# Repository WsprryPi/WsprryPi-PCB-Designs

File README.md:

# WsprryPi PCB Designs

KiCad schematics, PCB layouts, local libraries, and engineering documentation for WsprryPi and Raspberry Pi Pico projects.

See each project's order status, assembly requirements, and validation limits before fabrication. KiCad source files are authoritative; included PDFs are reference exports and may not match the current sources.

## Experimental use and warranty

All designs are provided **as is, without warranty**, as stipulated by the [MIT license](LICENSE.md) for repository-owned work. These are experimental hardware systems. They should not be used for production work unless the operator understands the design's limitations, assembly and power requirements, calibration needs, and the validation required for the actual system and operating conditions.

The operator is responsible for determining suitability and verifying the assembled hardware. A clean CAD check or a fabrication-ready layout does not establish electrical, RF, thermal, mechanical, or system performance. Third-party assets retain their documented licenses and notices.

## Projects

| Project | Purpose | Status / reference export |
| --- | --- | --- |
| [WsprryPi LPF](WsprryPi%20LPF/README.md) | Low-pass filter board and design workbook | Export from the KiCad source |
| [Pico 2W Wattmeter Shield](Pico%202W%20Wattmeter%20Shield/README.md) | ADL5904 RF detector and ADS1115 ADC shield | See project assembly drawings |
| [Pico 2W Shield Template](Pico%202W%20Shield%20Template/README.md) | Unwired shield interface, outline, and antenna notch | KiCad project template |
| [WsprryPico GPIO Shield](WsprryPico%20GPIO%20Shield/README.md) | Pico 2 W shield with the grouped BS170 amplifier circuit and independent local libraries | Placed and routed GPIO design; see current validation |
| [WsprryPico Synth Shield with GPS](WsprryPico%20Synth%20Shield%20with%20GPS/README.md) | Pico 2 W TCXO/Si5351A shield with a BS170 amplifier and onboard GNSS | Implemented PCB for the 2200 m–10 m target; see current validation and bias setup |
| [QRP Labs Modules](QRP%20Labs%20Modules/README.md) | Electrical models of the photographed 25 MHz TCXO and Rev6 synthesizer, with their interconnection | [Reference schematic PDF](QRP%20Labs%20Modules/QRP%20Labs%20Modules.pdf); separate from the proposed synth shield |
| [RPi Full-Size HAT Template](RPi%20Full-Size%20HAT%20Template/README.md) | Official full-size HAT geometry and complete 40-pin interface | KiCad project template |
| [RPi Zero HAT Template](RPi%20Zero%20HAT%20Template/README.md) | Zero-size uHAT geometry and complete HAT+ capable 40-pin interface | KiCad project template |
| [WsprryPi Zero GPIO BS170](WsprryPi%20Zero%20GPIO%20BS170/README.md) | Zero-size Raspberry Pi GPIO RF amplifier with a single BS170 | **Ready for order:** headers and BS170 fitted by hand after manufacture; see [fabrication and assembly notes](WsprryPi%20Zero%20GPIO%20BS170/FABRICATION-NOTES.md) |

[Project-local Pico 2 W library assets](Pico%202W%20Wattmeter%20Shield/pico-2w-libs/README.md) include a symbol, footprints, and STEP model with documented compatibility and provenance limits. They are stored inside the Wattmeter Shield project; the Shield Template uses its own independent local libraries.

## Open a design

Clone [WsprryPi/WsprryPi-PCB-Designs](https://github.com/WsprryPi/WsprryPi-PCB-Designs) into a folder named `WsprryPi PCB Designs` and open the project's `.kicad_pro` file in KiCad. Read its README for assembly requirements, dependencies, and validation limits. Follow the applicable template's instructions to create a new shield or HAT project.

| Project | Saved schematic and PCB generator version |
| --- | --- |
| WsprryPi LPF, Pico 2W Wattmeter Shield, Pico 2W Shield Template, WsprryPico GPIO Shield, WsprryPico Synth Shield with GPS, RPi Full-Size HAT Template, RPi Zero HAT Template, WsprryPi Zero GPIO BS170 | KiCad 10.0 |

Project library tables use `${KIPRJMOD}` paths. Keep each project's local libraries together when copying it. The Pico and HAT projects use their own local libraries and installed KiCad models where their project documentation specifies them.

### Project-local libraries

The LPF includes local copies of its symbols and footprints, plus available STEP models, resolved through `${KIPRJMOD}`. Its local library assets require KiCad 10.0.1 or newer; the generator version above describes its saved format. The other projects maintain their own independent local libraries as described in their READMEs.

- [LPF library contents and limits](WsprryPi%20LPF/libraries/README.md)
- [BS170 amplifier library sources and limits](WsprryPi%20Zero%20GPIO%20BS170/LIBRARY-SOURCES.md)

Project documentation records model gaps, assembly exclusions, and the applicability of ERC/DRC findings to the identified source revision. Order readiness does not establish measured electrical, thermal, or RF performance.

## Design proposals

These documents describe proposed circuits and outstanding engineering requirements; they do not establish implemented or validated hardware.

- [GPS frequency calibration for Pi and Pico](design/GPS-FREQUENCY-CALIBRATION.md): LS7366R capture of Si5351 CLK2 against GPS PPS.
- [Broadband RF amplifier HAT](design/raspberry-pi-hat-broadband-rf-amplifier.md): a proposed clock-input amplifier, power control, and supply architecture.

## Repository contents

Track design sources, local libraries, reusable models, design calculations, intentional reference exports, and documentation. Preserve legacy cache or rescue libraries required by a design.

The root [`.gitignore`](.gitignore) covers KiCad local preferences, locks, caches, automatic backups, `.history`, and `jlcpcb/` plugin state and output throughout the repository. Put regenerable exports in `generated/`, `production/`, or `fabrication/`.

Publish manufacturing packages with the corresponding GitHub release, identifying the source commit, board revision, KiCad version, and validation status. Keep assembly and fabrication requirements in the project's maintained documentation.

## Contributions and license

See [CONTRIBUTING.md](CONTRIBUTING.md) for editing and validation requirements. Report problems through [GitHub Issues](https://github.com/WsprryPi/WsprryPi-PCB-Designs/issues). [AGENTS.md](AGENTS.md) contains shared agent guidance; [CLAUDE.md](CLAUDE.md) points to it.

Repository-owned work uses the [MIT license](LICENSE.md). Preserve third-party copyright, attribution, and license terms; project and library documentation identifies known exceptions and provenance limits.

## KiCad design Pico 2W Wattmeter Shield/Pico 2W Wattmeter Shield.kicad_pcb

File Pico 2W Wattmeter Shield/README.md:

# Pico 2W QRP Wattmeter Shield

A Raspberry Pi Pico 2 W shield with an ADL5904 RF power detector, ADS1115 ADC, and TPS7A2033 analog regulator. Open [Pico 2W Wattmeter Shield.kicad_pro](Pico%202W%20Wattmeter%20Shield.kicad_pro) in KiCad 10. Project libraries use `${KIPRJMOD}` paths.

The design is supplied **as is, without warranty**, under the repository's [MIT license](../LICENSE.md). It is an experimental system. Production use requires an operator who understands its limitations and requirements and verifies the assembled system's suitability. See the [repository notice](../README.md#experimental-use-and-warranty).

## Current design

The PCB is a two-layer, nominally 1.6 mm FR4 board with circuit components on F.Cu and U10's two female socket strips on B.Cu, matching the [Pico shield template](../Pico%202W%20Shield%20Template/README.md). It contains **37 footprints: 34 automatic SMT components, J30, U10, and one front silkscreen logo**. The components, including the R63/C61 pull-up supply filter, are placed and routed.

Assembled input match, accuracy, noise rejection, mechanical fit, and the soldering process are unqualified. ERC ignores single-use global labels, four-way junctions, simulation model issues, and footprint-filter mismatches; DRC has no ignored checks.

## Measurement path

`J30 → C30–C34 → RF_DET_IN → C40–C44 → RFIN/U40 → VRMS_RAW → R50/C50 → VRMS_FILTERED/U60 AIN0`

| Section | Saved design |
| --- | --- |
| RF input | J30; terminating low-power meter, with external attenuation for amplifier outputs |
| Coupling | Two banks of five parallel 100 nF C0G capacitors, nominally 500 nF per bank |
| Shunt load | R30–R34: five parallel 412 Ω resistors, nominally 82.4 Ω, plus the detector input branch |
| Input matching | The shunt is within 0.12% of ADI's 82.5 Ω reference; assembled input impedance is unmeasured |
| Intended frequency range | 136 kHz–450 MHz, covering 2200 m through 70 cm; assembled-board coverage is unqualified |
| Nominal detector range | −30 to +15 dBm, approximately 1 µW–31.6 mW; connector range requires calibration |
| ADC filter | R50 = 470 Ω, C50 = 22 µF X5R; nominal cutoff 15.4 Hz |

There is no onboard attenuation pad or qualified high-power overload protection. The two capacitor banks, buses, launch, and detector impedance form a frequency-dependent RF network. See [input range and measurement conditions](INPUT-RANGE.md). The printed current range is calculated for a nominal 50 Ω load, rather than a direct current measurement.

## Power

**The analog section requires VBUS.** U20 takes VBUS from Pico pin 40 and generates `ANALOG_3V3` for U40, U60, and the I²C pullups. C20 and C21 are 2.2 µF, 25 V X7R capacitors at the regulator input and output. C46/C47 decouple the detector, and C60 decouples the ADC. The Pico's 3V3 output is not connected to the analog rail.

USB normally supplies VBUS. Powering the Pico solely through VSYS leaves the analog section unpowered. An external VBUS source must respect the Pico's USB power arrangement and avoid conflicting supplies. Measurements require a valid analog rail and settled detector/filter output.

VBUS follows the lower perimeter, and the analog rail reaches the detector from below and the ADC/control branch from the right. Neither supply trace crosses the RF capacitor-bank area. R63/C61 isolate the pull-up supply branch. A common regulator and ground serve the analog and I²C loads; noise immunity to Pico activity is unmeasured.

## ADC and filtering

U60 uses AIN0 as a single-ended detector-voltage input. ADDR is grounded, giving I²C address 0x48. SDA uses GP4; SCL uses GP5 through the fitted R62 0 Ω jumper. R60/R61 are 4.7 kΩ pullups supplied through R63 = 47 Ω, with C61 = 1 µF X7R providing local bypass at their common supply node. This filter is present in both schematic and PCB. U40 and U60 receive `ANALOG_3V3` directly with their own decoupling. Unused ADC channels and ALERT/RDY have no-connect flags.

R63/C61 has a nominal **3.4 kHz** corner and approximately **65 mV** supply drop with both pull-ups low, assuming ideal low output levels. It provides local storage and supply isolation for switching currents. Its effect on the assembled noise floor is unmeasured; nominal attenuation at 50/60 Hz is negligible.

R50/C50 passes DC and attenuates changing voltage. Its ideal one-pole attenuation is about **10.6 dB at 50 Hz and 12.1 dB at 60 Hz**, with a 10.34 ms time constant and about 47.6 ms settling to 1%. Capacitor tolerance, bias, temperature, detector output impedance, and ADC loading affect these figures. It is not a mains notch filter, and there is no established system-level mains-rejection specification. C49 remains a separate 10 nF capacitor directly on VRMS.

The hardware provides one measurement channel. ADC range, conversion rate, timed averaging, and calibration coefficients are application settings; this repository does not establish a verified wattmeter firmware configuration.

## Current assembly and fabrication

Factory assembly comprises **34 components on F.Cu**: **C20–C21, C30–C34, C40–C50, C60–C61; R30–R34, R40, R50, R60–R63; U20, U40, U60**. This is 20 capacitors, 11 resistors, and three ICs. J30, two female sockets, and the Pico module are fitted by hand. U10 represents the combined 40-pad socket interface; schematic J10/J11 are pinless purchasing descriptions. The front logo and manual parts are excluded from automatic SMT assembly.

The **Shield purchasing BOM** preset uses `LCSC Part #`. All 34 schematic and PCB SMT parts have matching manufacturer, MPN, and LCSC identifiers. R30–R34 specify Viking ARG02BTC4120 / C2683017 in local 0402 footprints. R63 specifies YAGEO RC0402FR-0747RL / C137973 in 0402; C61 specifies YAGEO CC0603KRX7R8BB105 / C106858 in 0603. Factory BOM and placement exports must contain the same 34 references and correct U20/U40/U60 pin-1 orientation. The schematic contains the complete part selections. The input-range silkscreen displays J30 through a reference variable and follows reannotation.

Seven selected through vias use **0.60 mm copper / 0.25 mm drill** with filling/capping enabled, F-side untented, and B-side tented: five in U40's exposed ground pad and one each centered on R40 pad 1 and C48 pad 1. The unique drill size identifies this selective process. The 17 ordinary vias comprise five 0.50/0.20 mm, ten 0.60/0.30 mm, and two 0.80/0.40 mm vias. All 24 are through vias; the custom rules disallow blind, buried, and microvias. The ordinary ground-via drills beside C45/C47 have **0.15 mm nominal clearance** from the adjacent component solder-pad openings.

The required fabrication process is selective nonconductive epoxy filling, planarization, and copper capping. Its availability for this exact two-layer order is not confirmed. Four separate 0.65 × 0.65 mm F.Paste windows cover 52.16% of U40's 1.8 × 1.8 mm ground land. Supplier process acceptance, stencil thickness, and reflow conditions are assembly requirements.

- [Fabrication and assembly requirements](manufacturing-notes/ORDER-NOTES.txt)
- [Front assembly map](manufacturing-notes/ASSEMBLY-FRONT.svg)
- [Selective via-treatment drawing](manufacturing-notes/U1-VIA-TREATMENT.svg)
- [U40 exposed-pad and stencil geometry](U1-PASTE-WINDOWS.md)
- [SMA connector and board-edge fit](J1-CONNECTOR-NOTES.md)
- [Pico sockets and antenna notch](PICO-HEADERS-AND-NOTCH.md)

The manufacturing drawings identify their source PCB by SHA-256. Socket lead fit and mating height are unspecified. The PCB stackup's copper-finish field is `None`, and there are no dedicated board fiducials; finish and panel tooling belong in the order specification.

## Pico interface placement

U10 is locked at **(146.810, 90.750) mm, −90°, B.Cu**, and its `Raspberry Pi Pico 2W` group is locked. Its 40 pad positions match the template. The notch spans x = 164.46–173.46 mm and y = 82.86–96.86 mm, with a copper/component keepout on both layers.

In **Update PCB from Schematic**, leave **Re-link footprints to schematic symbols based on their reference designators** and **Override locks** unchecked. Normal symbol-ID matching preserves the interface identity and placement. [KiCad's update documentation](https://docs.kicad.org/10.0/en/pcbnew/pcbnew.html#updating_the_board_from_the_schematic) describes these options.

The two socket models belong to U10's combined footprint and use project-local paths. The reusable footprint contains the same references. The socket geometry is a generic preview, without a selected manufacturer or qualified mating stack.

## Libraries and 3D view

Local assets are in `pico-wattmeter.pretty/`, `pico-wattmeter.kicad_sym`, `pico-wattmeter.kicad_blocks/`, and `pico-wattmeter.3dshapes/`. See [footprint sources and licenses](pico-wattmeter.pretty/LIBRARY-SOURCES.md) and [model sources and limits](pico-wattmeter.3dshapes/README.md).

Select **View > 3D Viewer** in the PCB Editor. U40 uses the local CP-16-22 STEP model. U10 uses two local socket models. J30 uses the local illustrative Adafruit 1865 SMA model, pointing outward from the left board edge. Passives, U20, and U60 use installed KiCad models. All placed model references resolve in the checked KiCad installation.

The optional, unplaced Pico SMD footprint uses `${KIPRJMOD}/pico-2w-libs/Raspberrypi pico2 W.step`. That separate reference collection has [pin/pad, model-alignment, and provenance limitations](pico-2w-libs/README.md). It is not the placed socket interface.

`fabrication-toolkit-options.json` stores export preferences. KiCad sources contain the part identifiers, connectivity, layout, and assembly exclusions. Local preferences, backups, plugin state, and generated export directories are ignored by Git.

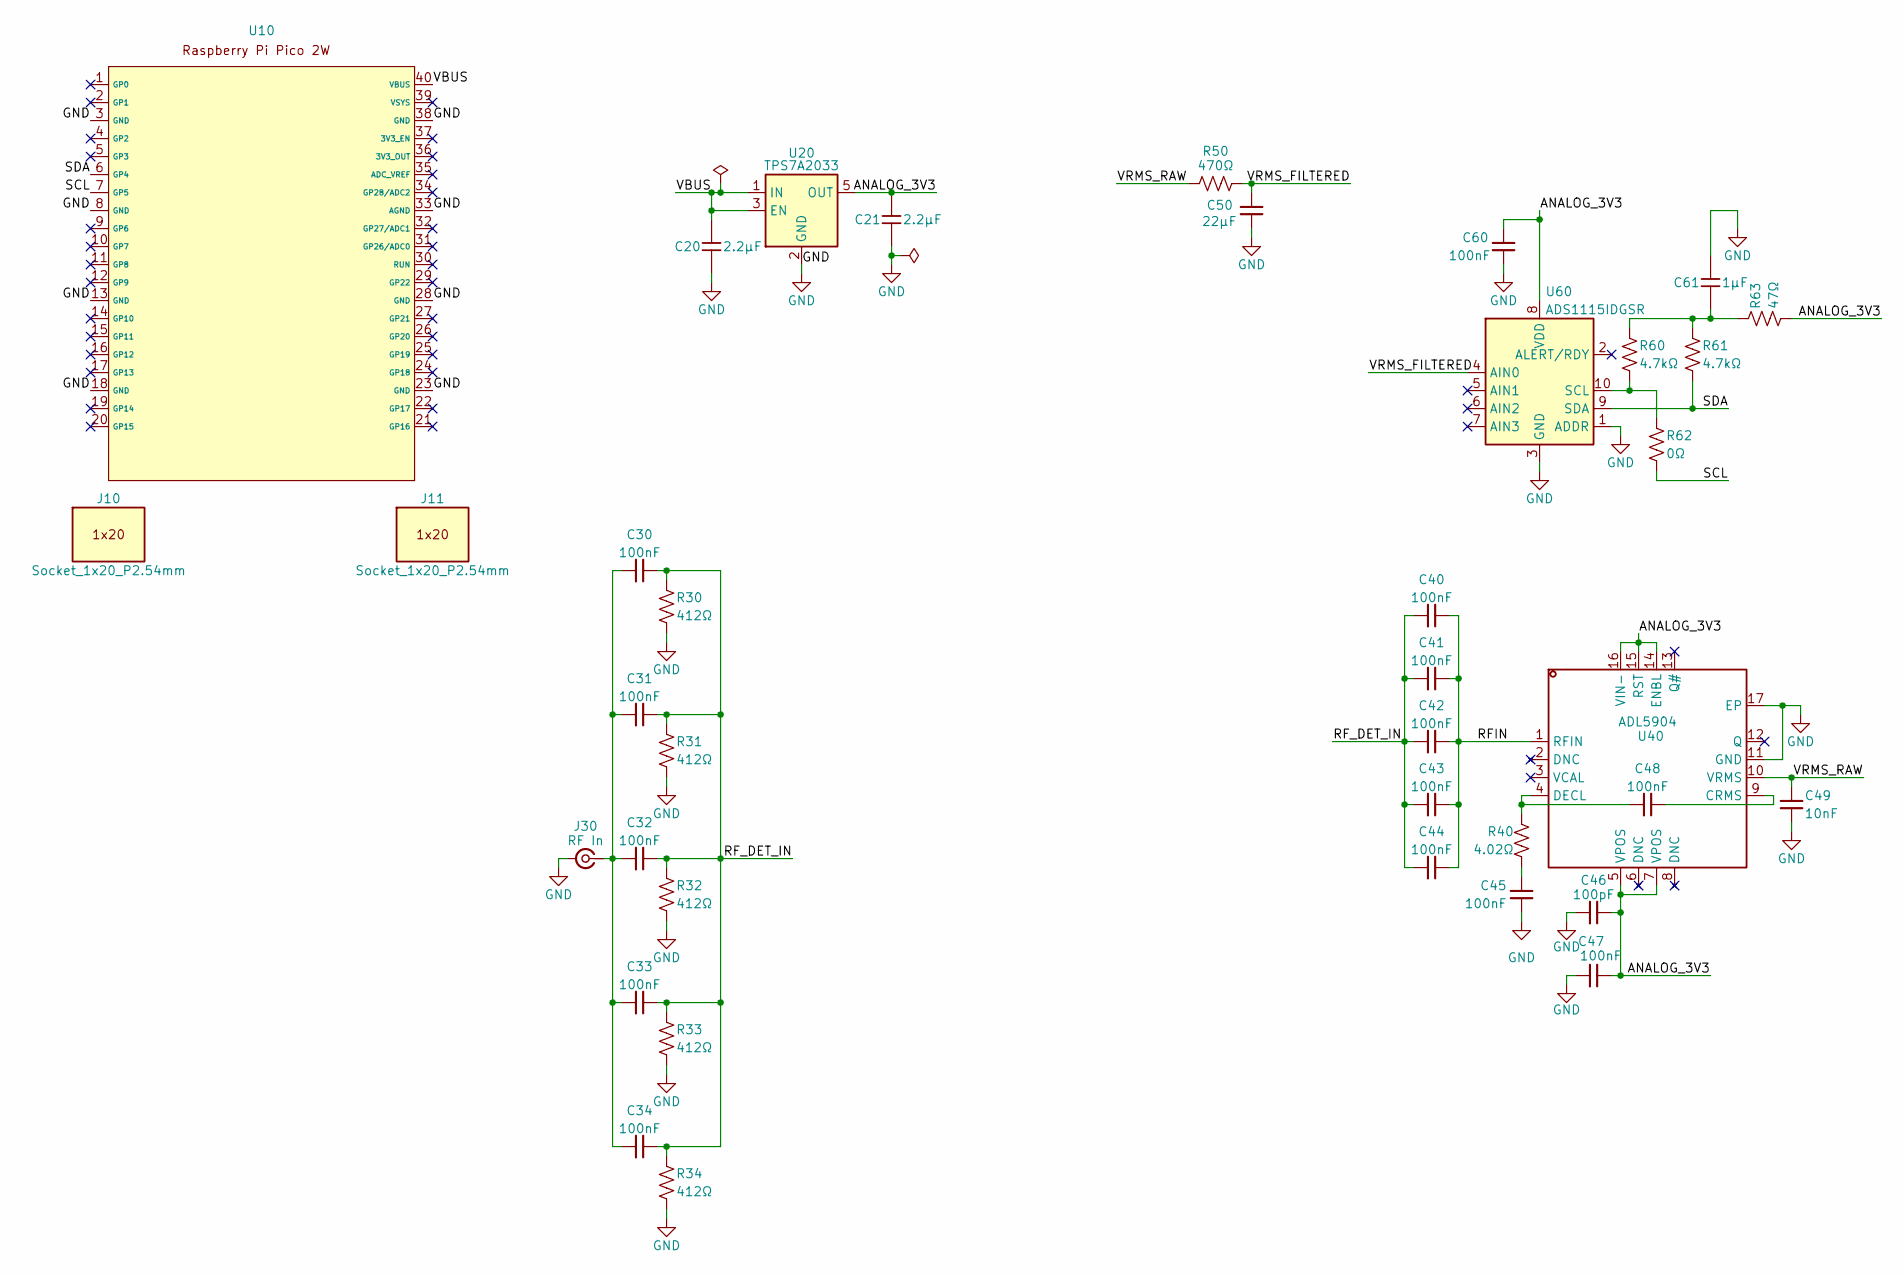
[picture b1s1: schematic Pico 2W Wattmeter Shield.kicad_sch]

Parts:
C20, C21: 2.2μF; C_0805_2012Metric; Tolerance 10%; Rating 25 V; MPN CC0805KKX7R8BB225; LCSC Part # C277470
C30, C31, C32, C33, C34, C40, C41, C42, C43, C44, C48: 100nF; C_1206_3216Metric; MPN 1206N104J500CT; LCSC Part # C170182
C45, C47, C60: 100nF; C_0402_1005Metric; MPN CL05B104KO5NNNC; LCSC Part # C1525
C46: 100pF; C_0402_1005Metric; MPN 0402CG101J500NT; LCSC Part # C1546
C49: 10nF; C_0402_1005Metric; MPN CL05B103KB5NNNC; LCSC Part # C15195
C50: 22µF; C_0805_2012Metric; MPN CL21A226MAYNNNE; LCSC Part # C602037
C61: 1μF; C_0603_1608Metric; Tolerance 10%; Rating 25 V; MPN CC0603KRX7R8BB105; LCSC Part # C106858
J10, J11: Socket_1x20_P2.54mm
J30: RF In; SMA_Adafruit_1865_EdgeMount; MPN 1865
R30, R31, R32, R33, R34: 412Ω; R_0402_1005Metric; MPN ARG02BTC4120; LCSC Part # C2683017
R40: 4.02Ω; R_0402_1005Metric; MPN FRC0402F4R02TS; LCSC Part # C55174786
R50: 470Ω; R_0402_1005Metric; MPN FRC0402F4700TS; LCSC Part # C2909361
R60, R61: 4.7kΩ; R_0402_1005Metric; MPN 0402WGF4701TCE; LCSC Part # C25900
R62: 0Ω; R_0805_2012Metric; MPN 0805W8F0000T5E; LCSC Part # C17477
R63: 47Ω; R_0402_1005Metric; MPN RC0402FR-0747RL; LCSC Part # C137973
U10: Raspberry_Pi_Pico_2W_Header
U20: TPS7A2033; SOT-23-5; Tolerance Datasheet; Rating 300 mA device rating; MPN TPS7A2033PDBVR; LCSC Part # C2862740
U40: ADL5904; QFN-16_L3.0-W3.0-P0.50-TL-EP1.8; MPN ADL5904ACPZN-R7; LCSC Part # C206813
U60: ADS1115IDGSR; TSSOP-10_3x3mm_P0.5mm; MPN ADS1115IDGSR; LCSC Part # C37593

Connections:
/ANALOG_3V3: C21.1, C46.2, C47.1, C60.2, R63.2, U20.5 (OUT), U40.5 (VPOS), U40.7 (VPOS), U40.14 (ENBL), U40.15 (RST), U40.16 (VIN-), U60.8 (VDD)
/RFIN: C40.2, C41.2, C42.2, C43.2, C44.2, U40.1 (RFIN)
/RF_DET_IN: C30.2, C31.2, C32.2, C33.2, C34.2, C40.1, C41.1, C42.1, C43.1, C44.1, R30.1, R31.1, R32.1, R33.1, R34.1
/SCL: R62.2, U10.7 (GP5)
/SDA: R61.2, U10.6 (GP4), U60.9 (SDA)
/VBUS: C20.1, U10.40 (VBUS), U20.1 (IN), U20.3 (EN)
/VRMS_FILTERED: C50.2, R50.2, U60.4 (AIN0)
/VRMS_RAW: C49.1, R50.1, U40.10 (VRMS)
GND: C20.2, C21.2, C45.2, C46.1, C47.2, C49.2, C50.1, C60.1, C61.1, J30.2 (GND), R30.2, R31.2, R32.2, R33.2, R34.2, U10.3 (GND), U10.8 (GND), U10.13 (GND), U10.18 (GND), U10.23 (GND), U10.28 (GND), U10.33 (AGND), U10.38 (GND), U20.2 (GND), U40.11 (GND), U40.17 (EP), U60.1 (ADDR), U60.3 (GND)
unnamed: C45.1, R40.2
unnamed: C61.2, R60.1, R61.1, R63.1
unnamed: C30.1, C31.1, C32.1, C33.1, C34.1, J30.1 (In)
unnamed: C48.2, U40.9 (CRMS)
unnamed: C48.1, R40.1, U40.4 (DECL)
unnamed: R60.2, R62.1, U60.10 (SCL)

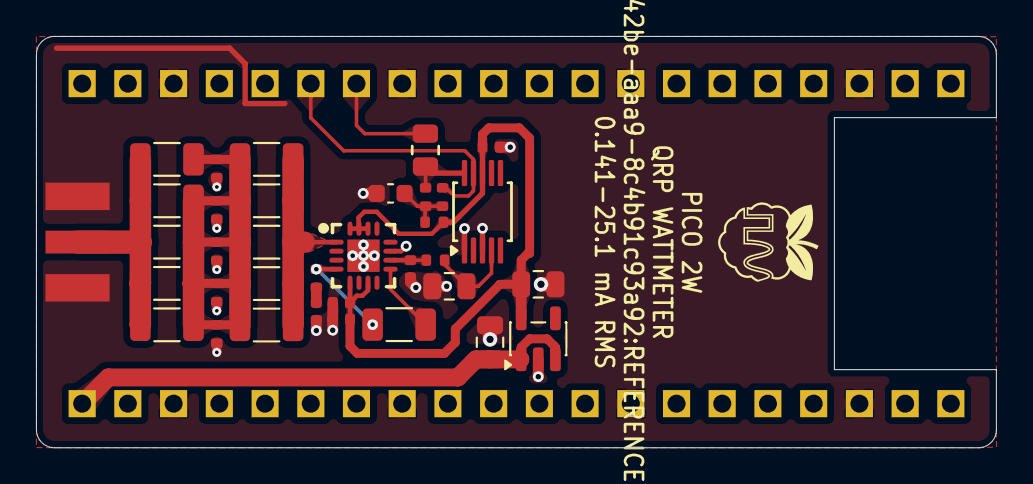
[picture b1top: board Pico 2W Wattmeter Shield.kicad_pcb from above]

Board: 2 copper layers, 53.3 x 22.9 mm, 37 parts (1 on the bottom side), 15 nets.

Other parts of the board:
LOGO2: Wsprry_Pi_Synth_Logo

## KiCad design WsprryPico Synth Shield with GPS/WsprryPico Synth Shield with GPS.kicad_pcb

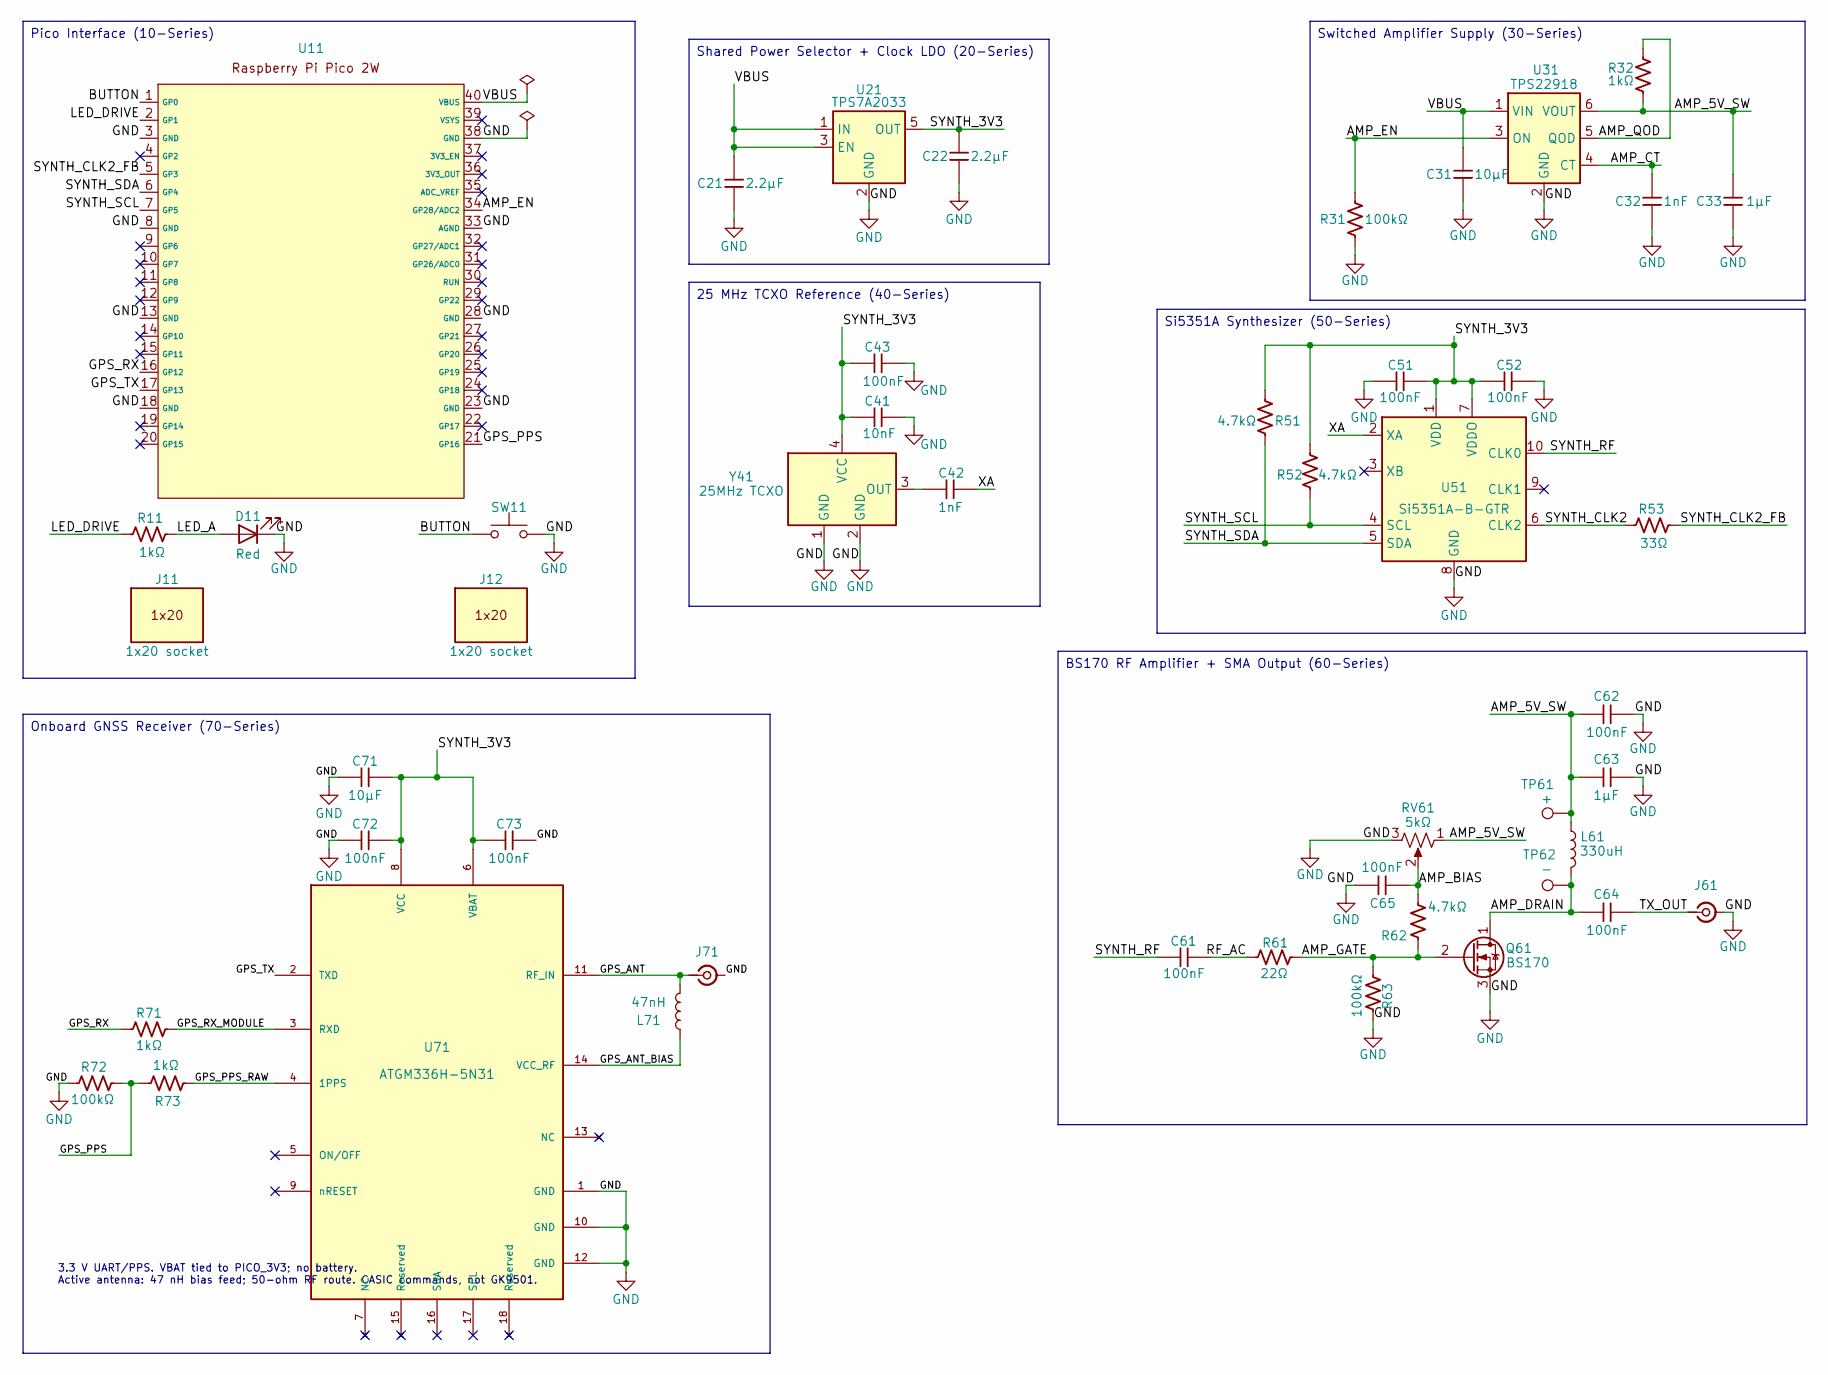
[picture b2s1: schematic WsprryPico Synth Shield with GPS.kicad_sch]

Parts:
C21, C22: 2.2μF; C_0805_2012Metric; Tolerance 10%; Rating 25 V; MPN CC0805KKX7R8BB225; LCSC Part # C277470
C31, C71: 10μF; C_1206_3216Metric; Tolerance 10%; Rating 25 V; MPN CL31B106KAHNNNE; LCSC Part # C14860
C32, C42: 1nF; C_0603_1608Metric; Tolerance 5%; Rating 50 V; MPN CC0603JRNPO9BN102; LCSC Part # C106246
C33, C63: 1μF; C_0805_2012Metric; Tolerance 10%; Rating 50 V; MPN AC0805KKX7R9BB105; LCSC Part # C726584
C41: 10nF; C_0603_1608Metric; Tolerance 10%; Rating 50 V; MPN FN18X103K500PSG; LCSC Part # C525264
C43, C51, C52, C62, C65, C72, C73: 100nF; C_0603_1608Metric; Tolerance 10%; Rating 50 V; MPN FN18X104K500PBG; LCSC Part # C235731
C61, C64: 100nF; C_1206_3216Metric; Tolerance 5%; Rating 50 V; MPN 1206N104J500CT; LCSC Part # C170182
D11: Red; LED_0603_1608Metric; Tolerance Datasheet; Rating 20 mA device rating; ~1 mA design; MPN KT-0603R; LCSC Part # C2286
J11, J12: 1x20 socket; Tolerance Drawing dimensions; Rating 2.5 A nominal; MPN PM2.54-1*20; LCSC Part # C5224030
J61: SMA 50ohm; SMA_Adafruit_1865_EdgeMount; Tolerance Drawing dimensions; Rating 50 ohm; MPN 1865
J71: U.FL 50ohm; U.FL_Hirose_U.FL-R-SMT-1_Vertical; Tolerance Drawing dimensions; Rating 50 ohm; MPN U.FL-R-SMT-1(10); LCSC Part # C88373
L61: 330uH; L_TDK_VLS6045EX_VLS6045AF; Tolerance 20%; Rating 500 mA at 30% L reduction; 470 mA at 40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; MPN VLS6045EX-331M; LCSC Part # C501933
L71: 47nH; L_0603_1608Metric; MPN LQW18AN47NG00D; LCSC Part # C98076
Q61: BS170; TO-92_Inline; Tolerance Datasheet; Rating 60 V / 500 mA device limits; MPN BS170; LCSC Part # C111691
R11, R32, R71, R73: 1kΩ; R_0603_1608Metric; Tolerance 1%; Rating 100 mW; 75 V; MPN RC0603FR-071KL; LCSC Part # C22548
R31, R63, R72: 100kΩ; R_0603_1608Metric; Tolerance 1%; Rating 100 mW; 75 V; MPN 0603WAF1003T5E; LCSC Part # C25803
R51, R52, R62: 4.7kΩ; R_0603_1608Metric; Tolerance 1%; Rating 100 mW; 75 V; MPN RC0603FR-074K7L; LCSC Part # C99782
R53: 33Ω; R_0603_1608Metric; Tolerance 1%; Rating 100 mW; 75 V; MPN 0603WAF330JT5E; LCSC Part # C23140
R61: 22Ω; R_0603_1608Metric; Tolerance 1%; Rating 100 mW; 75 V; MPN 0603WAF220JT5E; LCSC Part # C23345
RV61: 5kΩ; Potentiometer_Bourns_TC33X_Vertical; Tolerance 25%; Rating 150 mW; MPN TC33X-2-502E; LCSC Part # C719177
SW11: Push; SW_SPST_XUNPU_TS1088R_4x3mm; Tolerance Drawing dimensions; Rating 12 V / 50 mA contact rating; MPN TS-1088R-02026; LCSC Part # C455280
TP61: +; TestPoint_THTPad_1.0x1.0mm_Drill0.5mm
TP62: -; TestPoint_THTPad_1.0x1.0mm_Drill0.5mm
U11: Raspberry_Pi_Pico_2W_Header
U21: TPS7A2033; SOT-23-5; Tolerance Datasheet; Rating 300 mA device rating; MPN TPS7A2033PDBVR; LCSC Part # C2862740
U31: TPS22918; SOT-23-6; Tolerance Datasheet; Rating 5.5 V / 2 A device limits; MPN TPS22918DBVR; LCSC Part # C131941
U51: Si5351A-B-GTR; MSOP-10_Si5351A_3x3mm_P0.5mm; Tolerance Datasheet; Rating 3.3 V; MPN SI5351A-B-GTR; LCSC Part # C504891
U71: ATGM336H-5N31; Zhongke_ATGM336H-5N31_9.7x10.1mm_P1.1mm; MPN ATGM336H-5N31; LCSC Part # C90770
Y41: 25MHz TCXO; KDS_DSB321SDN_3.2x2.5mm; Tolerance Exact KDS specification; Rating 3.3 V; MPN 1XTW25000MAA; LCSC Part # C253672

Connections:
/AMP_5V_SW: C33.1, C62.1, C63.1, L61.1, R32.2, RV61.1, TP61.1 (1_1), U31.6 (VOUT)
/AMP_BIAS: C65.1, R62.1, RV61.2
/AMP_CT: C32.1, U31.4 (CT)
/AMP_DRAIN: C64.1, L61.2, Q61.1 (D), TP62.1 (1_1)
/AMP_EN: R31.1, U11.34 (GP28/ADC2), U31.3 (ON)
/AMP_GATE: Q61.2 (G), R61.2, R62.2, R63.1
/AMP_QOD: R32.1, U31.5 (QOD)
/BUTTON: SW11.1, U11.1 (GP0)
/GPS_ANT: J71.1 (In), L71.2, U71.11 (RF_IN)
/GPS_ANT_BIAS: L71.1, U71.14 (VCC_RF)
/GPS_PPS: R72.1, R73.2, U11.21 (GP16)
/GPS_PPS_RAW: R73.1, U71.4 (1PPS)
/GPS_RX: R71.2, U11.16 (GP12)
/GPS_RX_MODULE: R71.1, U71.3 (RXD)
/GPS_TX: U11.17 (GP13), U71.2 (TXD)
/LED_A: D11.2 (A), R11.2
/LED_DRIVE: R11.1, U11.2 (GP1)
/RF_AC: C61.2, R61.1
/SYNTH_3V3: C22.1, C41.1, C43.1, C51.1, C52.1, C71.1, C72.1, C73.1, R51.1, R52.1, U21.5 (OUT), U51.1 (VDD), U51.7 (VDDO), U71.6 (VBAT), U71.8 (VCC), Y41.4 (VCC)
/SYNTH_CLK2: R53.1, U51.6 (CLK2)
/SYNTH_CLK2_FB: R53.2, U11.5 (GP3)
/SYNTH_RF: C61.1, U51.10 (CLK0)
/SYNTH_SCL: R52.2, U11.7 (GP5), U51.4 (SCL)
/SYNTH_SDA: R51.2, U11.6 (GP4), U51.5 (SDA)
/TX_OUT: C64.2, J61.1 (In)
/VBUS: C21.1, C31.1, U11.40 (VBUS), U21.1 (IN), U21.3 (EN), U31.1 (VIN)
/XA: C42.2, U51.2 (XA)
GND: C21.2, C22.2, C31.2, C32.2, C33.2, C41.2, C43.2, C51.2, C52.2, C62.2, C63.2, C65.2, C71.2, C72.2, C73.2, D11.1 (K), J61.2 (GND), J71.2 (GND), Q61.3 (S), R31.2, R63.2, R72.2, RV61.3, SW11.2, U11.3 (GND), U11.8 (GND), U11.13 (GND), U11.18 (GND), U11.23 (GND), U11.28 (GND), U11.33 (AGND), U11.38 (GND), U21.2 (GND), U31.2 (GND), U51.8 (GND), U71.1 (GND), U71.10 (GND), U71.12 (GND), Y41.1 (GND), Y41.2 (GND)
unnamed: C42.1, Y41.3 (OUT)

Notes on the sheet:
3.3 V UART/PPS. VBAT tied to PICO_3V3; no battery. Active antenna: 47 nH bias feed; 50-ohm RF route. CASIC commands, not GK9501.
Switched Amplifier Supply (30-Series)
Pico Interface (10-Series)
Onboard GNSS Receiver (70-Series)
25 MHz TCXO Reference (40-Series)
Shared Power Selector + Clock LDO (20-Series)
Si5351A Synthesizer (50-Series)
BS170 RF Amplifier + SMA Output (60-Series)

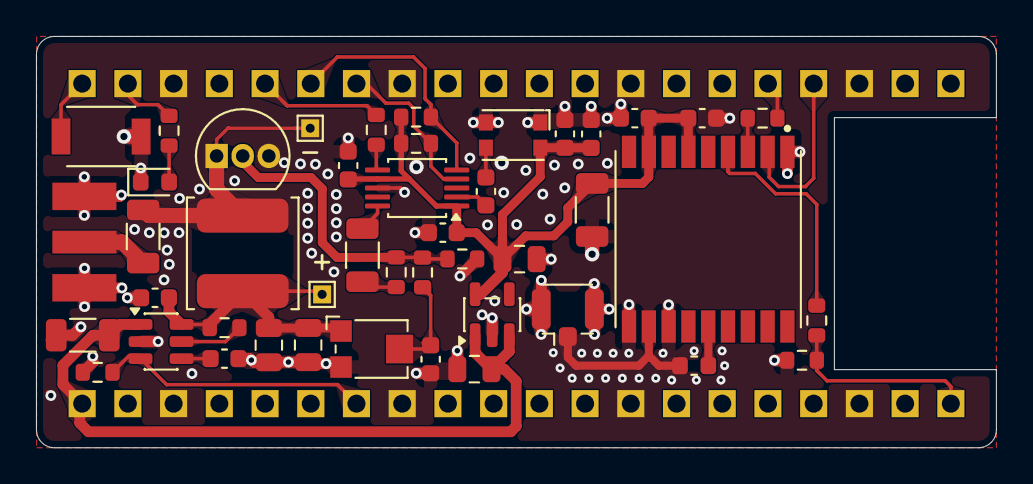
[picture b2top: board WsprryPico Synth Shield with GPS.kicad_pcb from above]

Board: 2 copper layers, 53.3 x 22.9 mm, 46 parts (1 on the bottom side), 29 nets.

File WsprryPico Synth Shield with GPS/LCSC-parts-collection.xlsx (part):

Reference | Value | Footprint | Dielectric or other qualifying info | Datasheet | Description | Manufacturer | MPN | LCSC Part #
R31 | 100kΩ | wsprrypico-synth-shield:R_0603_1608Metric | Thick film; 1%; 100 mW; 75 V | https://www.lcsc.com/datasheet/C25803.pdf | RES 100kΩ ±1% 100mW 0603 | UNI-ROYAL | 0603WAF1003T5E | C25803
R63 | 100kΩ | wsprrypico-synth-shield:R_0603_1608Metric | Thick film; 1%; 100 mW; 75 V | https://www.lcsc.com/datasheet/C25803.pdf | RES 100kΩ ±1% 100mW 0603 | UNI-ROYAL | 0603WAF1003T5E | C25803
R72 | 100kΩ | wsprrypico-synth-shield:R_0603_1608Metric | Thick film; 1%; 100 mW; 75 V | https://www.lcsc.com/datasheet/C25803.pdf | RES 100kΩ ±1% 100mW 0603 | UNI-ROYAL | 0603WAF1003T5E | C25803
C32 | 1nF | wsprrypico-synth-shield:C_0603_1608Metric | C0G / NP0; 5%; 50 V | https://www.lcsc.com/datasheet/C106246.pdf?spm=wm.sxq.inf.gg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 | CAP CER 1nF 50V NP0 0603 | YAGEO | CC0603JRNPO9BN102 | C106246
C42 | 1nF | wsprrypico-synth-shield:C_0603_1608Metric | C0G / NP0; 5%; 50 V | https://www.lcsc.com/datasheet/C106246.pdf?spm=wm.sxq.inf.gg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 | CAP CER 1nF 50V NP0 0603 | YAGEO | CC0603JRNPO9BN102 | C106246
C61 | 100nF | wsprrypico-synth-shield:C_1206_3216Metric | C0G / NP0; 5%; 50 V | https://www.lcsc.com/datasheet/C170182.pdf | CAP CER 100nF 50V NP0 1206 | Walsin | 1206N104J500CT | C170182
C64 | 100nF | wsprrypico-synth-shield:C_1206_3216Metric | C0G / NP0; 5%; 50 V | https://www.lcsc.com/datasheet/C170182.pdf | CAP CER 100nF 50V NP0 1206 | Walsin | 1206N104J500CT | C170182
C21 | 2.2μF | wsprrypico-synth-shield:C_0805_2012Metric | X7R; 10%; 25 V | https://www.lcsc.com/datasheet/C277470.pdf | CAP CER 2.2uF 25V X7R 0805 | YAGEO | CC0805KKX7R8BB225 | C277470
C22 | 2.2μF | wsprrypico-synth-shield:C_0805_2012Metric | X7R; 10%; 25 V | https://www.lcsc.com/datasheet/C277470.pdf | CAP CER 2.2uF 25V X7R 0805 | YAGEO | CC0805KKX7R8BB225 | C277470
C71 | 10uF | wsprrypico-synth-shield:C_1206_3216Metric | X7R; 10%; 25 V | https://www.lcsc.com/datasheet/C14860.pdf?spm=wm.sxq.inf.ggs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 | CAP CER 10uF 25V X7R 1206 | Samsung Electro-Mechanics | CL31B106KAHNNNE | C14860
C31 | 10μF | wsprrypico-synth-shield:C_1206_3216Metric | X7R; 10%; 25 V | https://www.lcsc.com/datasheet/C14860.pdf?spm=wm.sxq.inf.ggs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 | CAP CER 10uF 25V X7R 1206 | Samsung Electro-Mechanics | CL31B106KAHNNNE | C14860
C43 | 100nF | wsprrypico-synth-shield:C_0603_1608Metric | X7R; 10%; 50 V | https://www.lcsc.com/datasheet/C235731.pdf | CAP CER 100nF 50V X7R 0603 | PSA | FN18X104K500PBG | C235731
C51 | 100nF | wsprrypico-synth-shield:C_0603_1608Metric | X7R; 10%; 50 V | https://www.lcsc.com/datasheet/C235731.pdf | CAP CER 100nF 50V X7R 0603 | PSA | FN18X104K500PBG | C235731
C52 | 100nF | wsprrypico-synth-shield:C_0603_1608Metric | X7R; 10%; 50 V | https://www.lcsc.com/datasheet/C235731.pdf | CAP CER 100nF 50V X7R 0603 | PSA | FN18X104K500PBG | C235731
C62 | 100nF | wsprrypico-synth-shield:C_0603_1608Metric | X7R; 10%; 50 V | https://www.lcsc.com/datasheet/C235731.pdf | CAP CER 100nF 50V X7R 0603 | PSA | FN18X104K500PBG | C235731
R11 | 1kΩ | wsprrypico-synth-shield:R_0603_1608Metric | Thick film; 1%; 100 mW; 75 V | https://www.lcsc.com/datasheet/C22548.pdf | RES 1kΩ ±1% 100mW 0603 | YAGEO | RC0603FR-071KL | C22548
R32 | 1kΩ | wsprrypico-synth-shield:R_0603_1608Metric | Thick film; 1%; 100 mW; 75 V | https://www.lcsc.com/datasheet/C22548.pdf | RES 1kΩ ±1% 100mW 0603 | YAGEO | RC0603FR-071KL | C22548
R71 | 1kΩ | wsprrypico-synth-shield:R_0603_1608Metric | Thick film; 1%; 100 mW; 75 V | https://www.lcsc.com/datasheet/C22548.pdf | RES 1kΩ ±1% 100mW 0603 | YAGEO | RC0603FR-071KL | C22548
R73 | 1kΩ | wsprrypico-synth-shield:R_0603_1608Metric | Thick film; 1%; 100 mW; 75 V | https://www.lcsc.com/datasheet/C22548.pdf | RES 1kΩ ±1% 100mW 0603 | YAGEO | RC0603FR-071KL | C22548
C65 | 100nF | wsprrypico-synth-shield:C_0603_1608Metric | X7R; 10%; 50 V | https://www.lcsc.com/datasheet/C235731.pdf | CAP CER 100nF 50V X7R 0603 | PSA | FN18X104K500PBG | C235731
C72 | 100nF | wsprrypico-synth-shield:C_0603_1608Metric | X7R; 10%; 50 V | https://www.lcsc.com/datasheet/C235731.pdf | CAP CER 100nF 50V X7R 0603 | PSA | FN18X104K500PBG | C235731
J11 | 1x20 socket | wsprrypico-synth-shield:Raspberry_Pi_Pico_2W_Header | 2.54 mm pitch; 8.5 mm body; PBT; Au over Ni; 2.5 A nominal; manual fitting; sha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 |  | Pico female socket; purchased separately; PCB pads belong to U11 | ZHOURI | PM2.54-1*20 | C5224030
J12 | 1x20 socket | wsprrypico-synth-shield:Raspberry_Pi_Pico_2W_Header | 2.54 mm pitch; 8.5 mm body; PBT; Au over Ni; 2.5 A nominal; manual fitting; sha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 |  | Pico female socket; purchased separately; PCB pads belong to U11 | ZHOURI | PM2.54-1*20 | C5224030
C73 | 100nF | wsprrypico-synth-shield:C_0603_1608Metric | X7R; 10%; 50 V | https://www.lcsc.com/datasheet/C235731.pdf | CAP CER 100nF 50V X7R 0603 | PSA | FN18X104K500PBG | C235731
C41 | 10nF | wsprrypico-synth-shield:C_0603_1608Metric | X7R; 10%; 50 V | https://www.lcsc.com/datasheet/C525264.pdf | CAP CER 10nF 50V X7R 0603 | PSA | FN18X103K500PSG | C525264
C33 | 1μF | wsprrypico-synth-shield:C_0805_2012Metric | X7R; 10%; 50 V | https://www.lcsc.com/datasheet/C726584.pdf | CAP CER 1uF 50V X7R 0805 | YAGEO | AC0805KKX7R9BB105 | C726584
C63 | 1μF | wsprrypico-synth-shield:C_0805_2012Metric | X7R; 10%; 50 V | https://www.lcsc.com/datasheet/C726584.pdf | CAP CER 1uF 50V X7R 0805 | YAGEO | AC0805KKX7R9BB105 | C726584
R61 | 22Ω | wsprrypico-synth-shield:R_0603_1608Metric | Thick film; 1%; 100 mW; 75 V | https://www.lcsc.com/datasheet/C23345.pdf | RES 22Ω ±1% 100mW 0603 | UNI-ROYAL | 0603WAF220JT5E | C23345
Y41 | 25MHz TCXO | wsprrypico-synth-shield:KDS_DSB321SDN_3.2x2.5mm | TCXO; 3.3 V; 3.2 × 2.5 mm body; pins 1/2 GND, 3 OUT, 4 VCC | https://datasheet.lcsc.com/datasheet/pdf/4560f1646e80e1d25a3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 | Reference oscillator | KDS | 1XTW25000MAA | C253672
L61 | 330uH | wsprrypico-synth-shield:L_TDK_VLS6045EX_VLS6045AF | Factory wirewound ferrite; magnetic shield; SMT; 20%; 500 mA at 30% L reduction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 | https://product.tdk.com/system/files/dam/doc/product/inducto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 | Drain choke | TDK | VLS6045EX-331M | C501933
R53 | 33Ω | wsprrypico-synth-shield:R_0603_1608Metric | Thick film; 1%; 100 mW; 75 V | https://www.lcsc.com/datasheet/C23140.pdf | RES 33Ω ±1% 100mW 0603 | UNI-ROYAL | 0603WAF330JT5E | C23140
R51 | 4.7kΩ | wsprrypico-synth-shield:R_0603_1608Metric | Thick film; 1%; 100 mW; 75 V | https://www.lcsc.com/datasheet/C99782.pdf | RES 4.7kΩ ±1% 100mW 0603 | YAGEO | RC0603FR-074K7L | C99782
R52 | 4.7kΩ | wsprrypico-synth-shield:R_0603_1608Metric | Thick film; 1%; 100 mW; 75 V | https://www.lcsc.com/datasheet/C99782.pdf | RES 4.7kΩ ±1% 100mW 0603 | YAGEO | RC0603FR-074K7L | C99782
R62 | 4.7kΩ | wsprrypico-synth-shield:R_0603_1608Metric | Thick film; 1%; 100 mW; 75 V | https://www.lcsc.com/datasheet/C99782.pdf | RES 4.7kΩ ±1% 100mW 0603 | YAGEO | RC0603FR-074K7L | C99782
L71 | 47nH | wsprrypico-synth-shield:L_0603_1608Metric | Factory wirewound RF inductor; 2%; 380 mA; 0.29 ohm max DCR | https://www.lcsc.com/datasheet/C98076.pdf | GNSS active antenna DC bias RF choke | muRata | LQW18AN47NG00D | C98076
RV61 | 5kΩ | wsprrypico-synth-shield:Potentiometer_Bourns_TC33X_Vertical | Trimmer; 25%; 150 mW; pin 3 clockwise end; clockwise lowers bias | https://www.lcsc.com/datasheet/C719177.pdf | POT 5kΩ 150mW SMD-3P,3.8x3.6mm | BOURNS | TC33X-2-502E | C719177
U71 | ATGM336H-5N31 | wsprrypico-synth-shield:Zhongke_ATGM336H-5N31_9.7x10.1mm_P1.1mm | AT6558 GNSS receiver module; 2.7-3.6 V; 3.3 V UART/PPS | https://www.lcsc.com/datasheet/C90770.pdf | Onboard GPS/BDS receiver and PPS source | Hangzhou Zhongke Microelectronics | ATGM336H-5N31 | C90770
TP62 | BIAS- | wsprrypico-synth-shield:TestPoint_THTPad_1.0x1.0mm_Drill0.5mm | PCB copper; no separate part to order; AMP_DRAIN |  | L61 DC-drop measurement -; plated test pad
TP61 | BIAS+ | wsprrypico-synth-shield:TestPoint_THTPad_1.0x1.0mm_Drill0.5mm | PCB copper; no separate part to order; AMP_5V_SW |  | L61 DC-drop measurement +; plated test pad
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
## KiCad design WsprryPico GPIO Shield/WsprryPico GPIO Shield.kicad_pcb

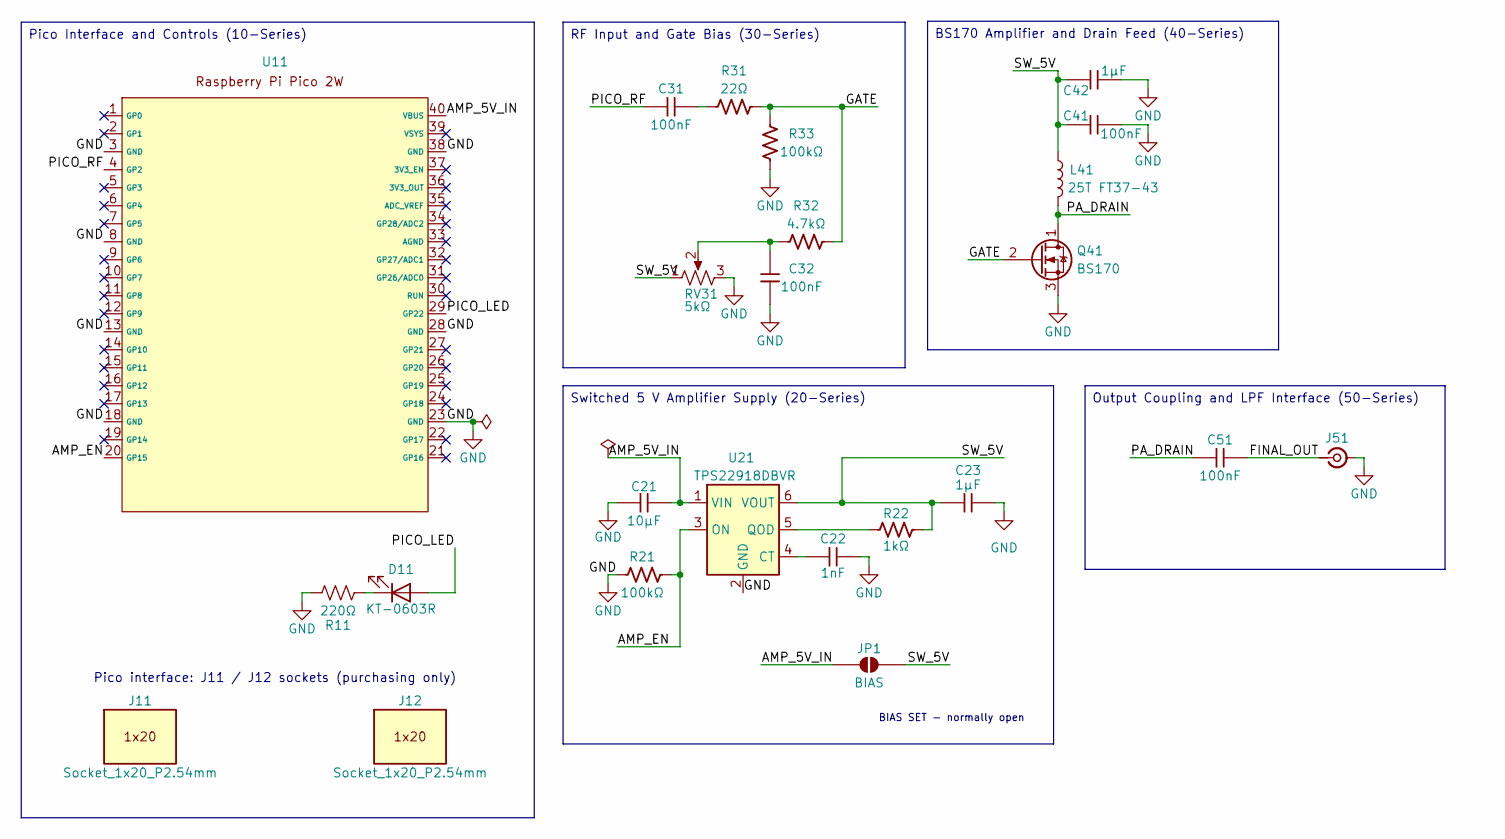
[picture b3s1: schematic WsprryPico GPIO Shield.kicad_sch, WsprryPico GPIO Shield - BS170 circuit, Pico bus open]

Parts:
C21: 10µF; C_0805_2012Metric; MPN CSA0805X5R106K250MT; LCSC Part # C20070397
C22: 1nF; C_0603_1608Metric; MPN CL10B102KB8NNNC; LCSC Part # C1588
C23, C42: 1µF; C_0805_2012Metric; MPN AC0805KKX7R9BB105; LCSC Part # C726584
C31, C51: 100nF; C_1206_3216Metric; MPN 1206N104J500CT; LCSC Part # C170182
C32, C41: 100nF; C_0603_1608Metric; MPN FN18X104K500PBG; LCSC Part # C235731
D11: KT-0603R; LED_0603_1608Metric; MPN KT-0603R; LCSC Part # C2286
J11, J12: Socket_1x20_P2.54mm
J51: SMA_Adafruit_1865; SMA_Adafruit_1865_EdgeMount; MPN 1865
JP1: BIAS; SolderJumper-2_P1.3mm_Open_RoundedPad1.0x1.5mm
L41: 25T FT37-43; L_Toroid_FT37-43_Vertical_P5.08mm; MPN FT-37-43 (core; wind 25 turns)
Q41: BS170; TO-92_Inline; MPN BS170
R11: 220Ω; R_0603_1608Metric; MPN FRC0603F2200TS; LCSC Part # C2907014
R21, R33: 100kΩ; R_0603_1608Metric; MPN 0603WAF1003T5E; LCSC Part # C25803
R22: 1kΩ; R_0603_1608Metric; MPN FRC0603F1001TS; LCSC Part # C2907002
R31: 22Ω; R_0603_1608Metric; MPN 0603WAF220JT5E; LCSC Part # C23345
R32: 4.7kΩ; R_0603_1608Metric; MPN 0603WAF4701T5E; LCSC Part # C23162
RV31: 5kΩ; Potentiometer_Bourns_TC33X_Vertical; MPN TC33X-2-502E; LCSC Part # C719177
U11: Raspberry_Pi_Pico_2W_Header
U21: TPS22918DBVR; SOT-23-6; MPN TPS22918DBVR; LCSC Part # C131941

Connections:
/AMP_5V_IN: C21.1, JP1.1 (A), U11.40 (VBUS), U21.1 (VIN)
/AMP_EN: R21.1, U11.20 (GP15), U21.3 (ON)
/FINAL_OUT: C51.2, J51.1 (In)
/GATE: Q41.2 (G), R31.2, R32.2, R33.2
/PA_DRAIN: C51.1, L41.2, Q41.1 (D)
/PICO_LED: D11.2 (A), U11.29 (GP22)
/PICO_RF: C31.1, U11.4 (GP2)
/SW_5V: C23.1, C41.1, C42.1, JP1.2 (B), L41.1, R22.1, RV31.1, U21.6 (VOUT)
GND: C21.2, C22.2, C23.2, C32.1, C41.2, C42.2, J51.2 (GND), Q41.3 (S), R11.2, R21.2, R33.1, RV31.3, U11.3 (GND), U11.8 (GND), U11.13 (GND), U11.18 (GND), U11.23 (GND), U11.28 (GND), U11.38 (GND), U21.2 (GND)
unnamed: C31.2, R31.1
unnamed: C32.2, R32.1, RV31.2
unnamed: D11.1 (K), R11.1
unnamed: C22.1, U21.4 (CT)
unnamed: R22.2, U21.5 (QOD)

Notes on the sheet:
Pico interface: J11 / J12 sockets (purchasing only)
BIAS SET - normally open
BS170 Amplifier and Drain Feed (40-Series)
RF Input and Gate Bias (30-Series)
Pico Interface and Controls (10-Series)
Switched 5 V Amplifier Supply (20-Series)
Output Coupling and LPF Interface (50-Series)

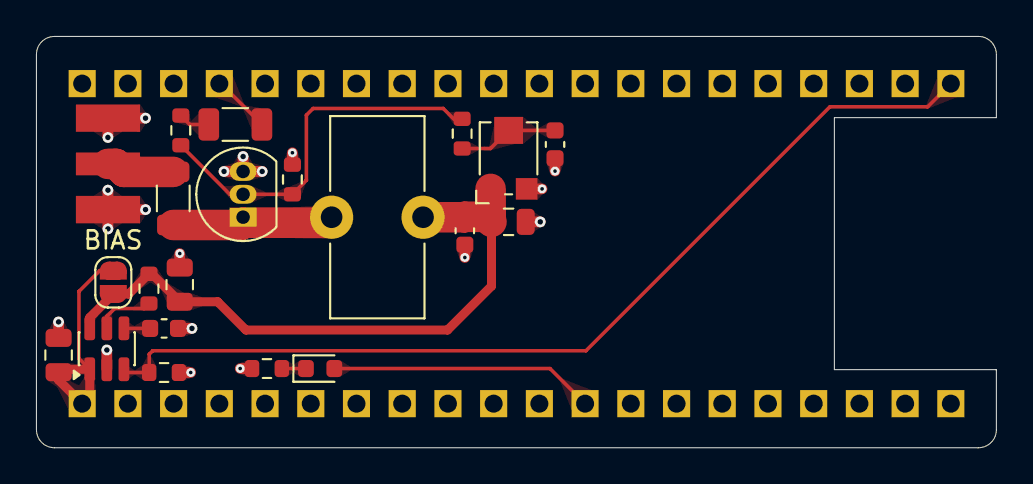
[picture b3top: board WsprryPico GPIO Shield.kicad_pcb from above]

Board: 2 copper layers, 53.3 x 22.9 mm, 22 parts (1 on the bottom side), 14 nets.

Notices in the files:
WsprryPico Synth Shield with GPS/WsprryPico Synth Shield with GPS.kicad_pcb:
Copyright © 2026
